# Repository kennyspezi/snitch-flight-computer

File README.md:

# Flight Compute Unit (FCU)
For future UAV and upcoming Omnimouse build (continuation of Micromouse)

## Schematics

## PCB (as of 08/18/2026)

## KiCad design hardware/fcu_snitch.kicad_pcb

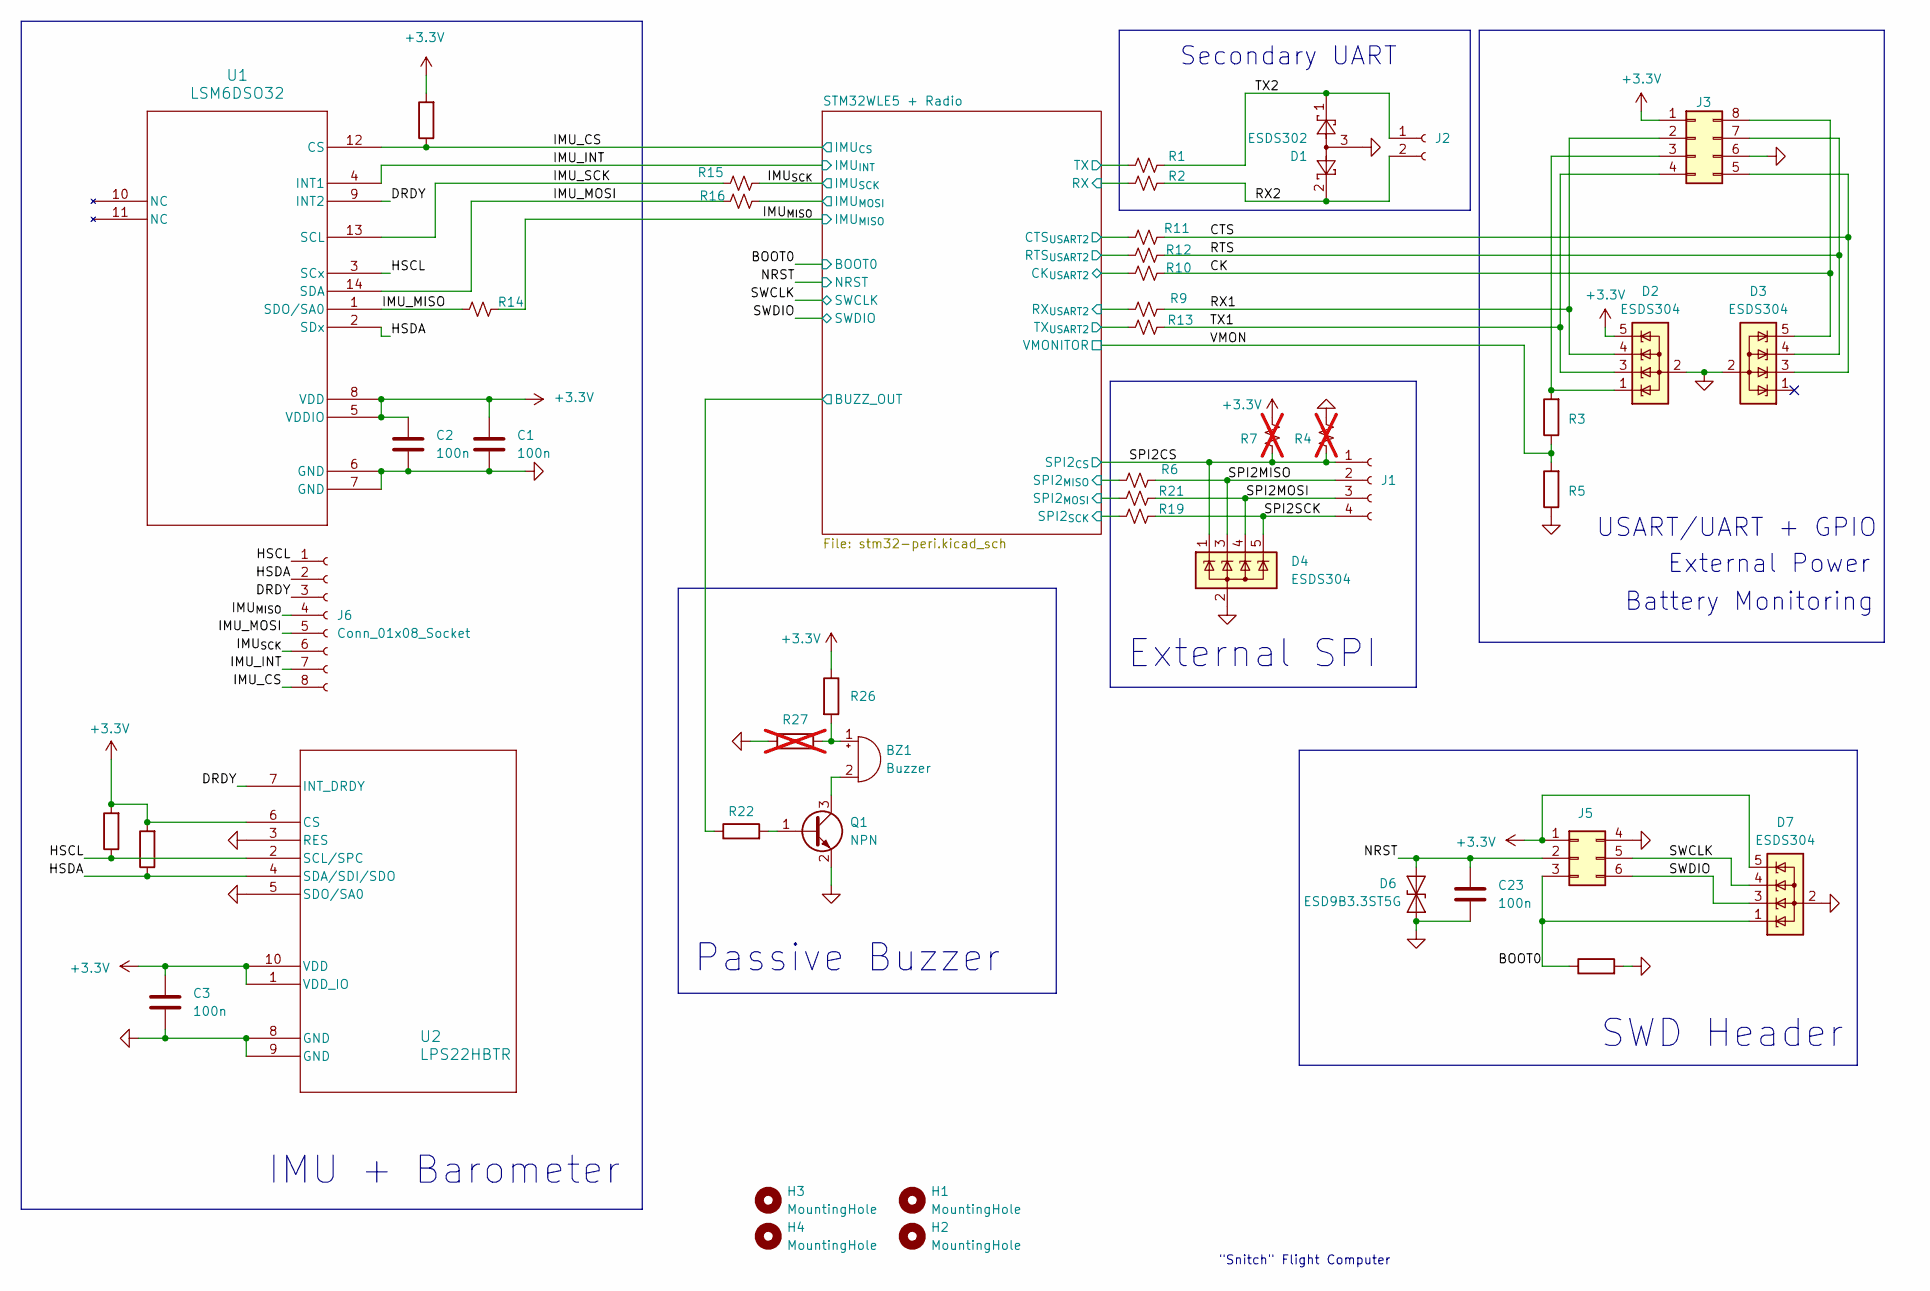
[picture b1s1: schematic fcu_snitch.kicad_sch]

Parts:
BZ1: Buzzer; CPT120303SMTTR
C1, C2, C3, C23: 100n; C_0805_2012Metric
D1: ESDS302; DBV0005A_M
D2, D3, D4, D7: ESDS304; SOT-23-5
D6: ESD9B3.3ST5G; D_SOD-923
H1, H2, H3, H4: MountingHole; MountingHole_2.2mm_M2
J1: Conn_01x04_Socket; JST_PH_S4B-PH-K_1x04_P2.00mm_Horizontal
J2: Conn_01x02_Socket; JST_PH_S2B-PH-K_1x02_P2.00mm_Horizontal
J3: Conn_02x04_Top_Bottom; JST_PHD_S8B-PHDSS_2x04_P2.00mm_Horizontal
J5: 02x03_JST_SWD; PinSocket_2x03_P1.00mm_Vertical_SMD
J6: Conn_01x08_Socket; PinHeader_1x08_P1.00mm_Horizontal
Q1: NPN; SOT-23
R1, R2, R6, R9, R10, R11, R12, R13, R14, R15, R16, R19, R21: R_Small_US; R_0805_2012Metric
R3, R5, R8, R17, R18, R22, R23, R26: R; R_0805_2012Metric
R4, R7: R_Small_US; R_0805_2012Metric; not fitted
R27: R; R_0805_2012Metric; not fitted
U1: LSM6DSO32; LGA-14L_2P5X3X0P83_STM-L
U2: LPS22HBTR; HLGA10_2X2_STM-L

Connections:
+3.3V: C1.1, C2.1, C3.1, D2.5 (K), D7.5 (K), J3.1, J5.1, R7.2, R8.2, R17.2, R18.2, R26.1, U1.5 (VDDIO), U1.8 (VDD), U2.1 (VDD_IO), U2.6 (CS), U2.10 (VDD); also elsewhere on the board
/BOOT0: D7.1 (K), J5.3, R23.1; also elsewhere on the board
/CK: D3.5 (K), J3.8, R10.2
/CTS: D3.3 (K), J3.5, R11.2
/DRDY: J6.3, U1.9 (INT2), U2.7 (INT_DRDY)
/HSCL: J6.1, R17.1, U1.3 (SCx), U2.2 (SCL/SPC)
/HSDA: J6.2, R18.1, U1.2 (SDx), U2.4 (SDA/SDI/SDO)
/IMU_CS: J6.8, R8.1, U1.12 (CS); also elsewhere on the board
/IMU_INT: J6.7, U1.4 (INT1); also elsewhere on the board
/IMU_MISO: R14.1, U1.1 (SDO/SA0)
/IMU_MOSI: J6.5, R16.1, U1.14 (SDA)
/IMU_SCK: R15.1, U1.13 (SCL)
/IMU_{MISO}: J6.4, R14.2; also elsewhere on the board
/IMU_{SCK}: J6.6, R15.2; also elsewhere on the board
/NRST: C23.1, D6.2 (A2), J5.2; also elsewhere on the board
/RTS: D3.4 (K), J3.7, R12.2
/RX1: D2.4 (K), J3.2, R9.2
/RX2: D1.2, J2.2, R2.2
/SPI2CS: D4.1 (K), J1.1, R4.1, R7.1; also elsewhere on the board
/SPI2MISO: D4.3 (K), J1.2, R6.2
/SPI2MOSI: D4.4 (K), J1.3, R21.2
/SPI2SCK: D4.5 (K), J1.4, R19.2
/STM32WLE5 + Radio/BUZZ_OUT: R22.1; also elsewhere on the board
/STM32WLE5 + Radio/CK_{USART2}: R10.1; also elsewhere on the board
/STM32WLE5 + Radio/CTS_{USART2}: R11.1; also elsewhere on the board
/STM32WLE5 + Radio/IMU_{MOSI}: R16.2; also elsewhere on the board
/STM32WLE5 + Radio/RTS_{USART2}: R12.1; also elsewhere on the board
/STM32WLE5 + Radio/RX: R2.1; also elsewhere on the board
/STM32WLE5 + Radio/RX_{USART2}: R9.1; also elsewhere on the board
/STM32WLE5 + Radio/SPI2_{MISO}: R6.1; also elsewhere on the board
/STM32WLE5 + Radio/SPI2_{MOSI}: R21.1; also elsewhere on the board
/STM32WLE5 + Radio/SPI2_{SCK}: R19.1; also elsewhere on the board
/STM32WLE5 + Radio/TX: R1.1; also elsewhere on the board
/STM32WLE5 + Radio/TX_{USART2}: R13.1; also elsewhere on the board
/SWCLK: D7.4 (K), J5.5; also elsewhere on the board
/SWDIO: D7.3 (K), J5.6; also elsewhere on the board
/TX1: D2.3 (K), J3.4, R13.2
/TX2: D1.1, J2.1, R1.2
/VMON: R3.1, R5.2; also elsewhere on the board
GND: C1.2, C2.2, C3.2, C23.2, D1.3, D2.2 (A), D3.2 (A), D4.2 (A), D6.1 (A1), D7.2 (A), J3.6, J5.4, Q1.2 (E), R4.2, R5.1, R23.2, R27.1, U1.6 (GND), U1.7 (GND), U2.3 (RES), U2.5 (SDO/SA0), U2.8 (GND), U2.9 (GND); also elsewhere on the board
unnamed: BZ1.1 (+), R26.2, R27.2
unnamed: BZ1.2 (-), Q1.3 (C)
unnamed: D2.1 (K), J3.3, R3.2
unnamed: Q1.1 (B), R22.2

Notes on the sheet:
External SPI
Secondary UART
Battery Monitoring
IMU + Barometer
USART/UART + GPIO
SWD Header
External Power
"Snitch" Flight Computer
Passive Buzzer

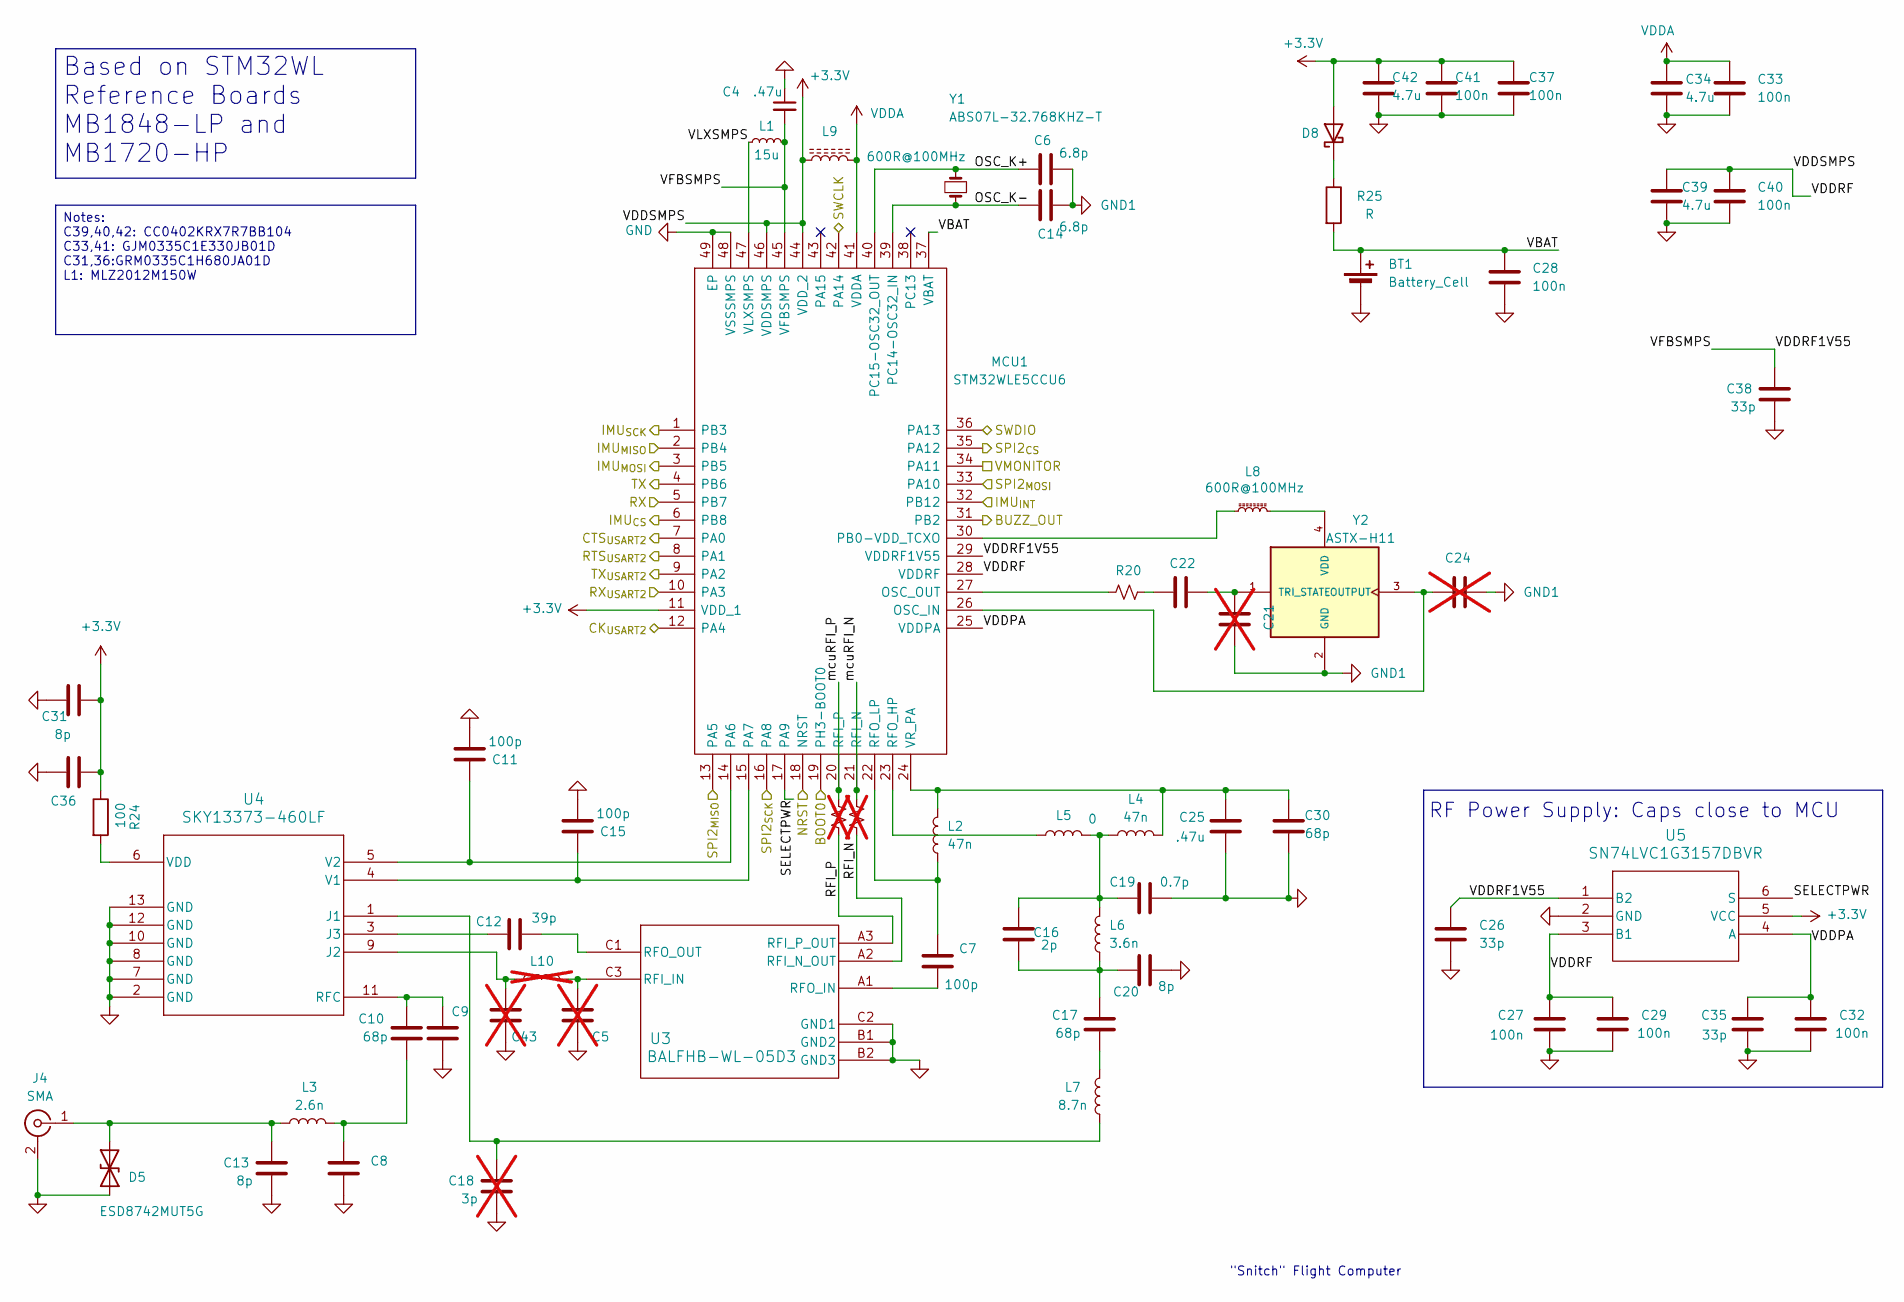
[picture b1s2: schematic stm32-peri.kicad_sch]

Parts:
BT1: Battery_Cell; BatteryHolder_Keystone_3034_1x20mm
C4, C25: .47u; C_0805_2012Metric
C5: 100p; C_0402_1005Metric; not fitted
C6, C14: 6.8p; C_0805_2012Metric
C7, C11, C15: 100p; C_0402_1005Metric
C8, C9: C_0402_1005Metric
C10, C17: 68p; C_0402_1005Metric
C12: 39p; C_0402_1005Metric
C13, C20: 8p; C_0402_1005Metric
C16: 2p; C_0402_1005Metric
C18: 3p; C_0402_1005Metric; not fitted
C19: 0.7p; C_0402_1005Metric
C21, C24: C; C_0805_2012Metric; not fitted
C22: C; C_0805_2012Metric
C26, C35: 33p; C_0402_1005Metric
C27, C29, C32: 100n; C_0402_1005Metric
C28, C33, C37, C40, C41: 100n; C_0805_2012Metric
C30: 68p; C_0805_2012Metric
C31: 8p; C_0805_2012Metric
C34, C39, C42: 4.7u; C_0805_2012Metric
C36: C_0805_2012Metric
C38: 33p; C_0805_2012Metric
C43: 8p; C_0402_1005Metric; not fitted
D5: ESD8742MUT5G; X3DFN2_ONS
D8: D_Schottky; D_SMA
J4: SMA; SMA_Amphenol_132289_EdgeMount
L1: 15u; L_0402_1005Metric
L2, L4: 47n; L_0402_1005Metric
L3: 2.6n; L_0402_1005Metric
L5: 0; L_0402_1005Metric
L6: 3.6n; L_0402_1005Metric
L7: 8.7n; L_0402_1005Metric
L8, L9: 600R@100MHz; IND_BLM18KG601SN1D_MUR-M
L10: 3.6n; L_0402_1005Metric; not fitted
MCU1: STM32WLE5CCU6; QFN50P700X700X60-49N-D; Mouser Part Number 511-STM32WLE5CCU6
R20: R_Small_US; R_0805_2012Metric
R24: 100; R_0805_2012Metric
R25: R; R_0805_2012Metric
R28, R29: R_Small_US; R_0201_0603Metric_Pad0.64x0.40mm_HandSolder; not fitted
U3: BALFHB-WL-05D3; BGA8_BALFHB_STM
U4: SKY13373-460LF; SKY13373-460LF_SKY
U5: SN74LVC1G3157DBVR; DBV6
Y1: ABS07L-32.768KHZ-T; XTAL_ABS07L-32.768KHZ-T; PARTREV 02.07.13
Y2: ASTX-H11; XTAL_ASTX-H11-32.000MHZ-I25-T; PARTREV 05.13.15

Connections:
+3.3V: C27.1, C29.1, C31.1, C36.1, C37.1, C39.1, C40.1, C41.1, C42.1, D8.2 (A), L9.1, MCU1.11 (VDD_1), MCU1.28 (VDDRF), MCU1.44 (VDD_2), MCU1.46 (VDDSMPS), R24.1, U5.3 (B1), U5.5 (VCC); also elsewhere on the board
/BOOT0: MCU1.19 (PH3-BOOT0); also elsewhere on the board
/IMU_CS: MCU1.6 (PB8); also elsewhere on the board
/IMU_INT: MCU1.32 (PB12); also elsewhere on the board
/IMU_{MISO}: MCU1.2 (PB4); also elsewhere on the board
/IMU_{SCK}: MCU1.1 (PB3); also elsewhere on the board
/NRST: MCU1.18 (NRST); also elsewhere on the board
/SPI2CS: MCU1.35 (PA12); also elsewhere on the board
/STM32WLE5 + Radio/BUZZ_OUT: MCU1.31 (PB2); also elsewhere on the board
/STM32WLE5 + Radio/CK_{USART2}: MCU1.12 (PA4); also elsewhere on the board
/STM32WLE5 + Radio/CTS_{USART2}: MCU1.7 (PA0); also elsewhere on the board
/STM32WLE5 + Radio/IMU_{MOSI}: MCU1.3 (PB5); also elsewhere on the board
/STM32WLE5 + Radio/OSC_K+: C6.1, MCU1.40 (PC15-OSC32_OUT), Y1.2
/STM32WLE5 + Radio/OSC_K-: C14.1, MCU1.39 (PC14-OSC32_IN), Y1.1
/STM32WLE5 + Radio/RFI_N: R29.2, U3.A2 (RFI_N_OUT)
/STM32WLE5 + Radio/RFI_P: R28.2, U3.A3 (RFI_P_OUT)
/STM32WLE5 + Radio/RTS_{USART2}: MCU1.8 (PA1); also elsewhere on the board
/STM32WLE5 + Radio/RX: MCU1.5 (PB7); also elsewhere on the board
/STM32WLE5 + Radio/RX_{USART2}: MCU1.10 (PA3); also elsewhere on the board
/STM32WLE5 + Radio/SELECTPWR: MCU1.17 (PA9), U5.6 (S)
/STM32WLE5 + Radio/SPI2_{MISO}: MCU1.13 (PA5); also elsewhere on the board
/STM32WLE5 + Radio/SPI2_{MOSI}: MCU1.33 (PA10); also elsewhere on the board
/STM32WLE5 + Radio/SPI2_{SCK}: MCU1.16 (PA8); also elsewhere on the board
/STM32WLE5 + Radio/TX: MCU1.4 (PB6); also elsewhere on the board
/STM32WLE5 + Radio/TX_{USART2}: MCU1.9 (PA2); also elsewhere on the board
/STM32WLE5 + Radio/VBAT: BT1.1 (+), C28.1, MCU1.37 (VBAT), R25.2
/STM32WLE5 + Radio/VDDPA: C32.1, C35.1, MCU1.25 (VDDPA), U5.4 (A)
/STM32WLE5 + Radio/VDDRF1V55: C4.2, C26.1, C38.1, L1.2, MCU1.29 (VDDRF1V55), MCU1.45 (VFBSMPS), U5.1 (B2)
/STM32WLE5 + Radio/VLXSMPS: L1.1, MCU1.47 (VLXSMPS)
/STM32WLE5 + Radio/mcuRFI_N: MCU1.21 (RFI_N), R29.1
/STM32WLE5 + Radio/mcuRFI_P: MCU1.20 (RFI_P), R28.1
/SWCLK: MCU1.42 (PA14); also elsewhere on the board
/SWDIO: MCU1.36 (PA13); also elsewhere on the board
/VMON: MCU1.34 (PA11); also elsewhere on the board
GND: BT1.2 (-), C4.1, C5.1, C8.2, C9.2, C11.2, C13.2, C15.2, C18.2, C19.2, C20.2, C25.1, C26.2, C27.2, C28.2, C29.2, C30.1, C31.2, C32.2, C33.2, C34.2, C35.2, C36.2, C37.2, C38.2, C39.2, C40.2, C41.2, C42.2, C43.2, D5.1 (A1), J4.2 (Ext), MCU1.48 (VSSSMPS), MCU1.49 (EP), U3.B1 (GND2), U3.B2 (GND3), U3.C2 (GND1), U4.2 (GND), U4.7 (GND), U4.8 (GND), U4.10 (GND), U4.12 (GND), U4.13 (GND), U5.2 (GND); also elsewhere on the board
GND1: C6.2, C14.2, C21.2, C24.2, Y2.2 (GND)
unnamed: C8.1, C10.2, L3.2
unnamed: C16.1, C17.2, C20.1, L6.1
unnamed: C16.2, C19.1, L4.2, L5.2, L6.2
unnamed: C17.1, L7.2
unnamed: C22.1, R20.2
unnamed: C13.1, D5.2 (A2), J4.1 (In), L3.1
unnamed: D8.1 (K), R25.1
unnamed: C24.1, MCU1.26 (OSC_IN), Y2.3 (OUTPUT)
unnamed: MCU1.27 (OSC_OUT), R20.1
unnamed: C11.1, MCU1.14 (PA6), U4.5 (V2)
unnamed: C15.1, MCU1.15 (PA7), U4.4 (V1)
unnamed: L8.1, MCU1.30 (PB0-VDD_TCXO)
unnamed: L5.1, MCU1.23 (RFO_HP)
unnamed: C7.2, L2.2, MCU1.22 (RFO_LP)
unnamed: C25.2, C30.2, L2.1, L4.1, MCU1.24 (VR_PA)
unnamed: C5.2, L10.2, U3.C3 (RFI_IN)
unnamed: C7.1, U3.A1 (RFO_IN)
unnamed: C12.1, U3.C1 (RFO_OUT)
unnamed: C18.1, L7.1, U4.1 (J1)
unnamed: C43.1, L10.1, U4.9 (J2)
unnamed: C12.2, U4.3 (J3)
unnamed: C9.1, C10.1, U4.11 (RFC)
unnamed: R24.2, U4.6 (VDD)
unnamed: C21.1, C22.2, Y2.1 (TRI_STATE)
unnamed: L8.2, Y2.4 (VDD)
VDDA: C33.1, C34.1, L9.2, MCU1.41 (VDDA)

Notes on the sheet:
"Snitch" Flight Computer
RF Power Supply: Caps close to MCU
Based on STM32WL Reference Boards MB1848-LP and MB1720-HP
Notes: C39,40,42: CC0402KRX7R7BB104 C33,41: GJM0335C1E330JB01D C31,36:GRM0335C1H680JA01D L1: MLZ2012M150W

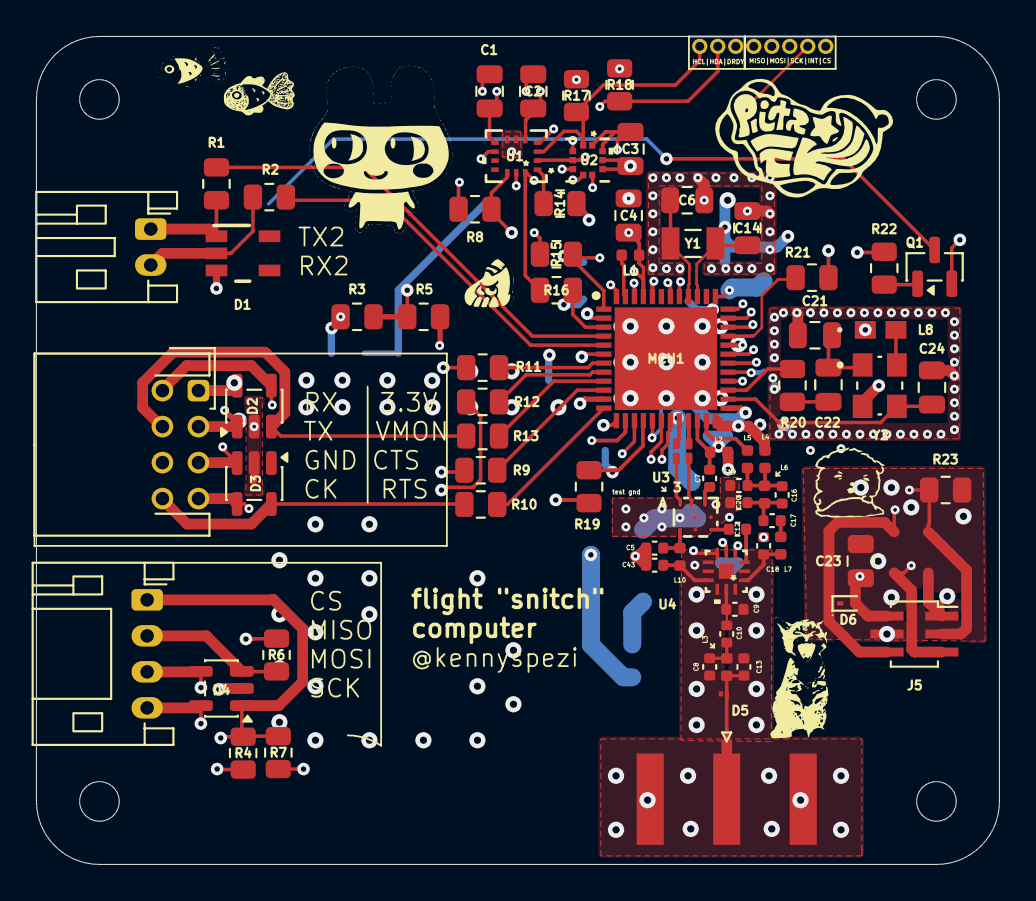
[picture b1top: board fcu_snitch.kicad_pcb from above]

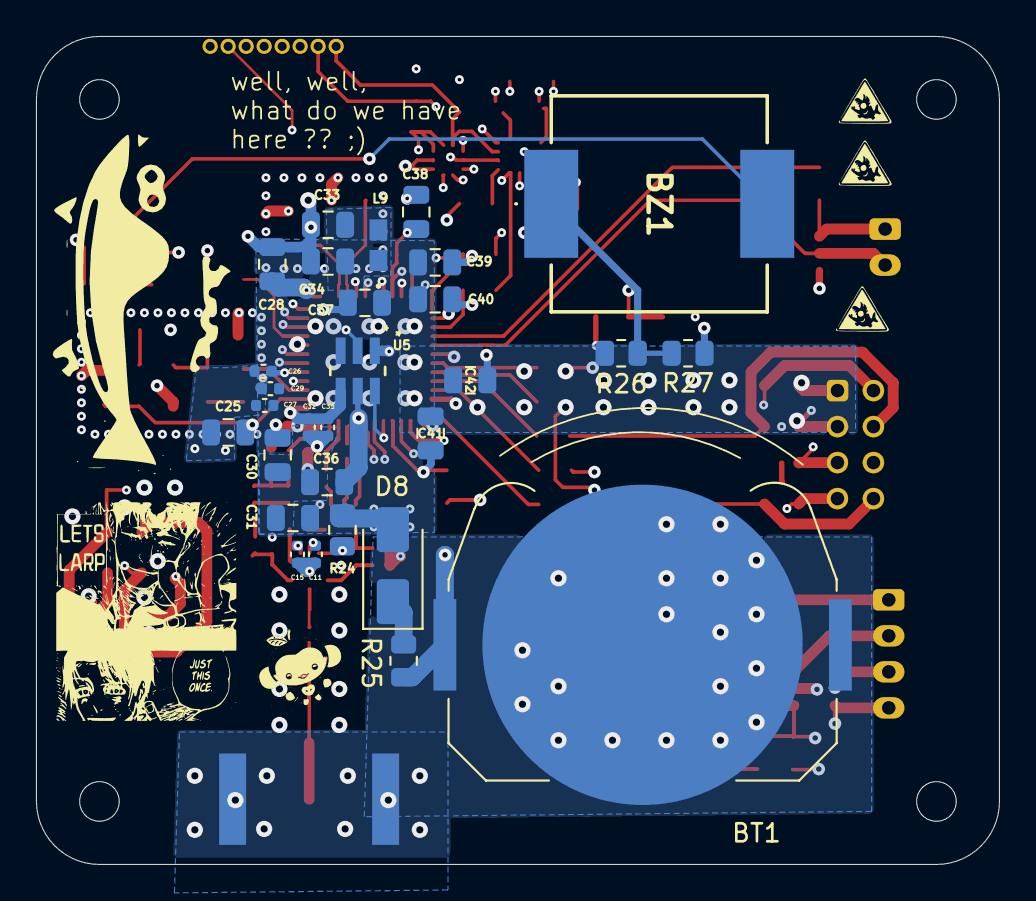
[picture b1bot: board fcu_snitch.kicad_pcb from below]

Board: 6 copper layers, 53.5 x 46.0 mm, 113 parts (29 on the bottom side), 82 nets.

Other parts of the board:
H3#2, H3#3, H3#4: MountingHole; MountingHole_2.2mm_M2
